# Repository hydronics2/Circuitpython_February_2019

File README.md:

# Circuitpython_February_2019
This is a soldering and programming class in Circuitpython

[github.com/hydronics2/circuitpython_february_2019](https://github.com/hydronics2/Circuitpython_February_2019)

This class occurs in two parts -- Soldering and Programming.

We'll be soldering parts and headers  onto a custom printed circuit board(PCB).  
Once complete, the microController (an Adfruit development board -  [ItsyBitsy M0](https://www.adafruit.com/product/3727)) sockets onto the PCB female headers.
When you connect the Adafruit M0 microController to your computer it shows up as an external hard drive with pre-loaded example scripts.

[Soldering Tutorial](https://github.com/hydronics2/Circuitpython_February_2019/blob/master/soldering/README.md)

[Programming Tutorial](https://github.com/hydronics2/Circuitpython_February_2019/blob/master/programming/README.md)

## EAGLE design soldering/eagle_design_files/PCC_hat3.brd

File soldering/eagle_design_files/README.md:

# Printed Circuit Board

This circuit board was designed in Eagle.

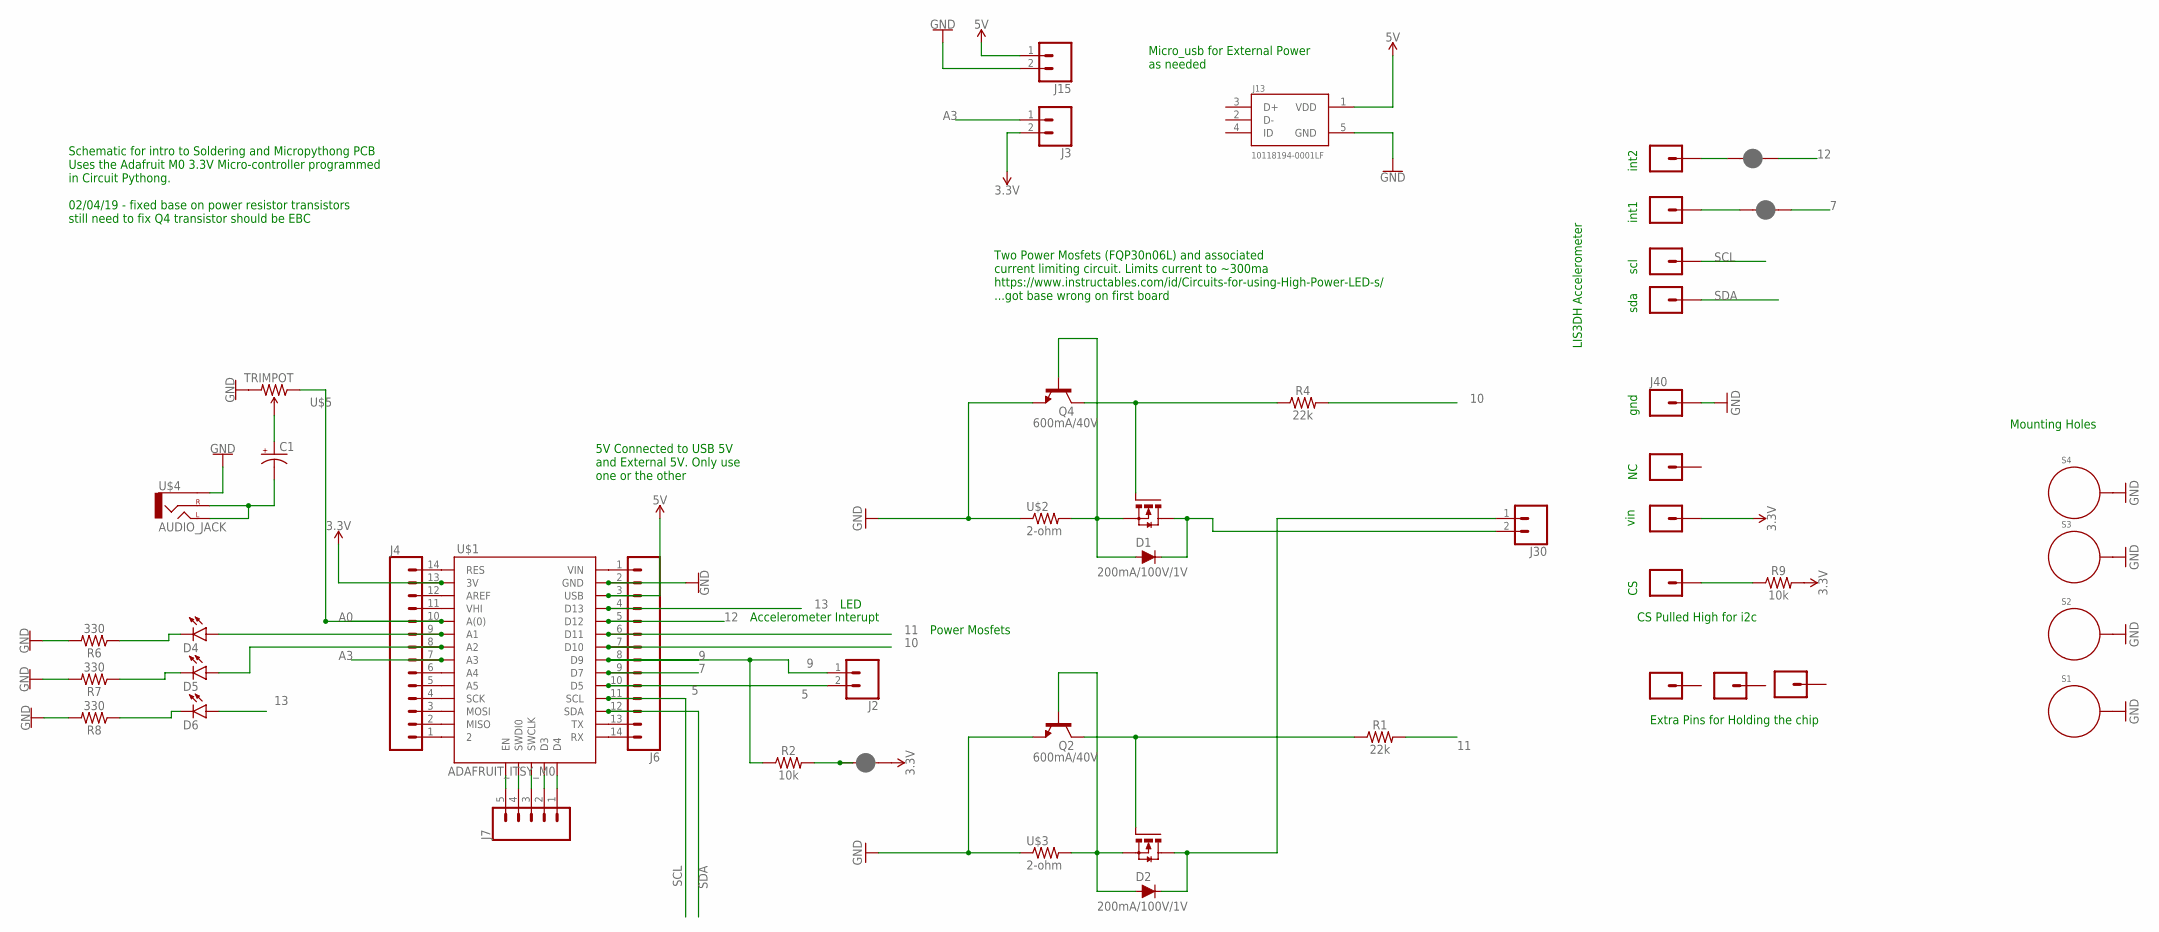
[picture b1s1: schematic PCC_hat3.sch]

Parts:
C1: CAP_POLPTH1; CPOL-RADIAL-100UF-25V
D1, D2: 200mA/100V/1V; DIODE-1N4148-KIT
D4, D5, D6: LED5MM
J2, J3, J15, J30: CONN_025MM; SCREWTERMINAL-5MM-2
J4, J6: CONN_14; 1X14
J5, J8, J9, J10, J11, J12, J39, J40, J42, J43, J44: M01PTH; 1X01
J7: CONN_05; 1X05
J13: 10118194-0001LF; FRAMATOME_10118194-0001LF
JP1, JP2, JP3: JUMPER-SMT_2_NC_PASTE_SILK; SMT-JUMPER_2_NC_PASTE_SILK
Q1, Q3: IRFI540NPBF; TO220BH
Q2, Q4: 600mA/40V; TO-92
R1, R4: 22k; AXIAL-0.3-KIT
R2, R9: 10k; AXIAL-0.3-KIT
R6, R7, R8: 330; AXIAL-0.3-KIT
S1, S2, S3, S4: STANDOFF_ELECTRICAL; STANDOFF-ELECTRICAL
U$1: ADAFRUIT_ITSY_M0; ADAFRUIT_ITS_M0
U$2, U$3: 2-ohm; RESISTOR_5W_PT
U$4: AUDIO_JACK; 1/8"AUDIO_JACK
U$5: TRIMPOT; 1X03_TRIMPOT

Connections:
3.3V: J3.2, J4.13, J5.1, JP3.2, R9.P$2 (2), U$1.3V
5: J2.2, J6.10, U$1.D5
5V: J6.3, J13.1 (VDD), J15.1, U$1.USB
7: J6.9, JP1.2, U$1.D7
9: J2.1, J6.8, R2.P$1 (1), U$1.D9
10: J6.7, R4.P$2 (2), U$1.D10
11: J6.6, R1.P$2 (2), U$1.D11
12: J6.5, JP2.2, U$1.D12
13: D6.A, J6.4, U$1.D13
A0: J4.10, U$1.A0 (A(0)), U$5.1 (CCW)
A3: J3.1, J4.7, U$1.A3
EXTERNAL_5V: J6.1, U$1.VIN
GND: J6.2, J13.5 (GND), J15.2, J40.1, Q2.3 (E), Q4.3 (E), R6.P$2 (2), R7.P$2 (2), R8.P$2 (2), S1.P1, S2.P1, S3.P1, S4.P1, U$1.GND, U$2.P$1 (1), U$3.P$1 (1), U$4.GND (SLEEVE), U$5.3 (CW)
unnamed: JP3.1, R2.P$2 (2)
unnamed: D4.K (C), R6.P$1 (1)
unnamed: J7.1, U$1.D4
unnamed: C1.2 (-), U$4.LEFT_TIP_1 (LEFT), U$4.RIGHT
unnamed: J4.2, U$1.MISO
unnamed: J4.3, U$1.MOSI
unnamed: J4.4, U$1.SCK
unnamed: J4.5, U$1.A5
unnamed: J4.6, U$1.A4
unnamed: C1.1 (+), U$5.2 (WIPER)
unnamed: D5.A, J4.8, U$1.A2
unnamed: D4.A, J4.9, U$1.A1
unnamed: D5.K (C), R7.P$1 (1)
unnamed: J4.11, U$1.VHI
unnamed: J4.12, U$1.AREF
unnamed: J4.14, U$1.RES
unnamed: D2.C, J30.1, Q1.D
unnamed: D1.A, Q3.S, Q4.2 (B), U$2.P$2 (2)
unnamed: J11.1, JP2.1
unnamed: D6.K (C), R8.P$1 (1)
unnamed: J6.13, U$1.TX
unnamed: J6.14, U$1.RX
unnamed: J7.2, U$1.3 (D3)
unnamed: J7.3, U$1.SWCLK
unnamed: J7.4, U$1.SWDI0
unnamed: J7.5, U$1.EN
unnamed: J44.1, JP1.1
unnamed: J8.1, R9.P$1 (1)
unnamed: D2.A, Q1.S, Q2.2 (B), U$3.P$2 (2)
unnamed: Q3.G, Q4.1 (C), R4.P$1 (1)
unnamed: Q1.G, Q2.1 (C), R1.P$1 (1)
unnamed: J4.1, U$1.2
unnamed: D1.C, J30.2, Q3.D
SCL: J6.11, J43.1, U$1.SCL
SDA: J6.12, J42.1, U$1.SDA

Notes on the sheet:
vin
gnd
sda
scl
int1
LIS3DH Accelerometer
CS Pulled High for i2c
int2
Power Mosfets
LED
Extra Pins for Holding the chip
Two Power Mosfets (FQP30n06L) and associated current limiting circuit. Limits current to ~300ma https://www.instructables.com/id/Circuits-for-using-High-Power-LED-s/ ...got base wrong on first board
Accelerometer Interupt
Mounting Holes
Micro_usb for External Power as needed
5V Connected to USB 5V and External 5V. Only use one or the other
Schematic for intro to Soldering and Micropythong PCB Uses the Adafruit M0 3.3V Micro-controller programmed in Circuit Pythong. 02/04/19 - fixed base on power resistor transistors still need to fix Q4 transistor should be EBC

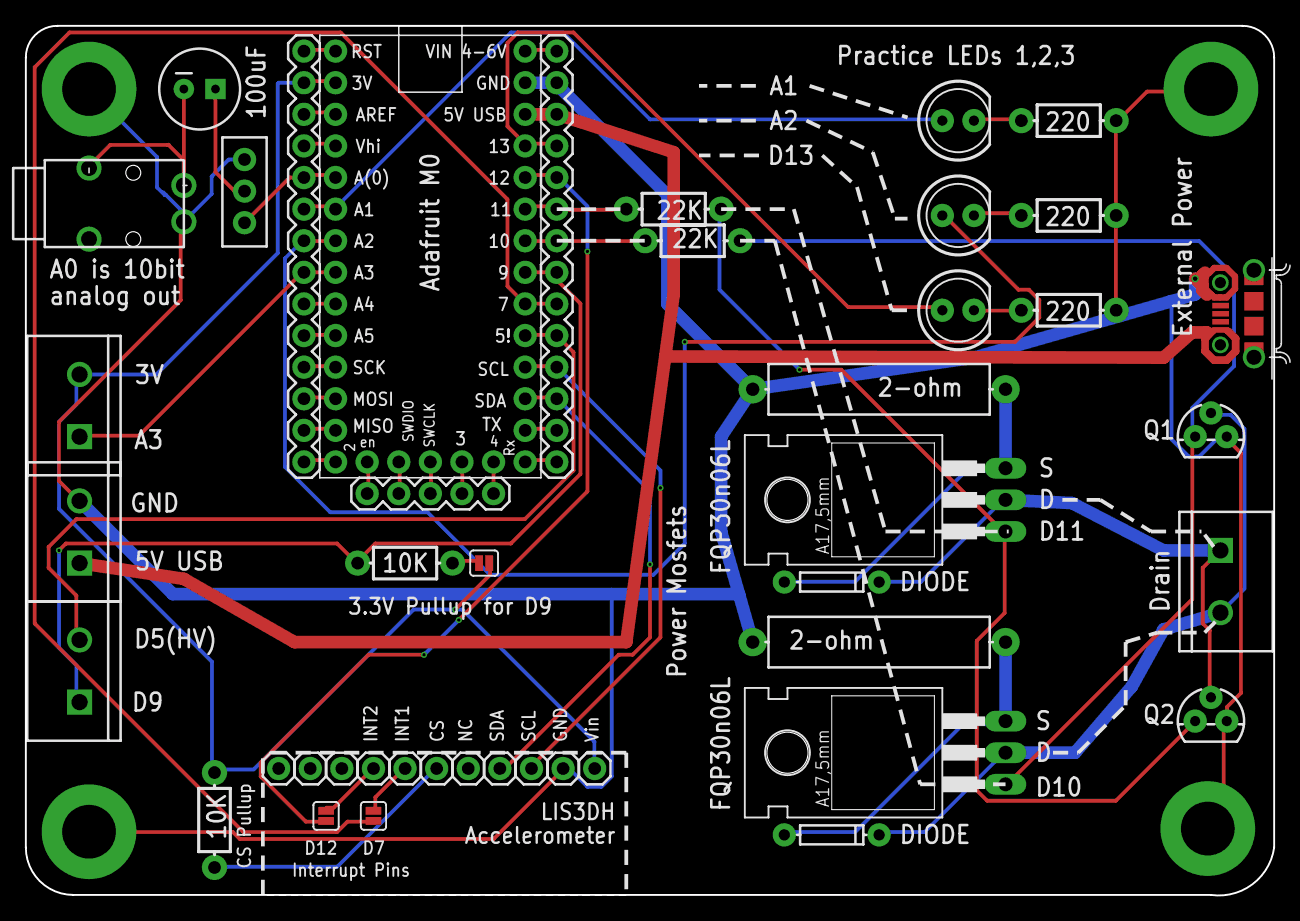
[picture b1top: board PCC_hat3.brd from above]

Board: 2 copper layers, 100.3 x 69.9 mm, 48 parts (0 on the bottom side), 48 nets.

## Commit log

2019-02-17 Create soldering tutorial
2019-02-17 Update soldering tutorial
2019-02-17 Create temp
2019-02-17 add python files
2019-02-17 added sounds
2019-02-23 updated solder instructions
2019-06-22 new class
2019-06-22 Revert "new class"
    This reverts commit 5374a47602157a0fa1197a82c1c2d07d4dc48a7c.

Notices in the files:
parts and their libraries:
SparkFun-Connectors: Licensing: CC v3.0 Share-Alike You are welcome to use this library for commercial purposes.
SparkFun-Passives: Licensing: Creative Commons ShareAlike 4.0 International - https://creativecommons.org/licenses/by-sa/4.0
